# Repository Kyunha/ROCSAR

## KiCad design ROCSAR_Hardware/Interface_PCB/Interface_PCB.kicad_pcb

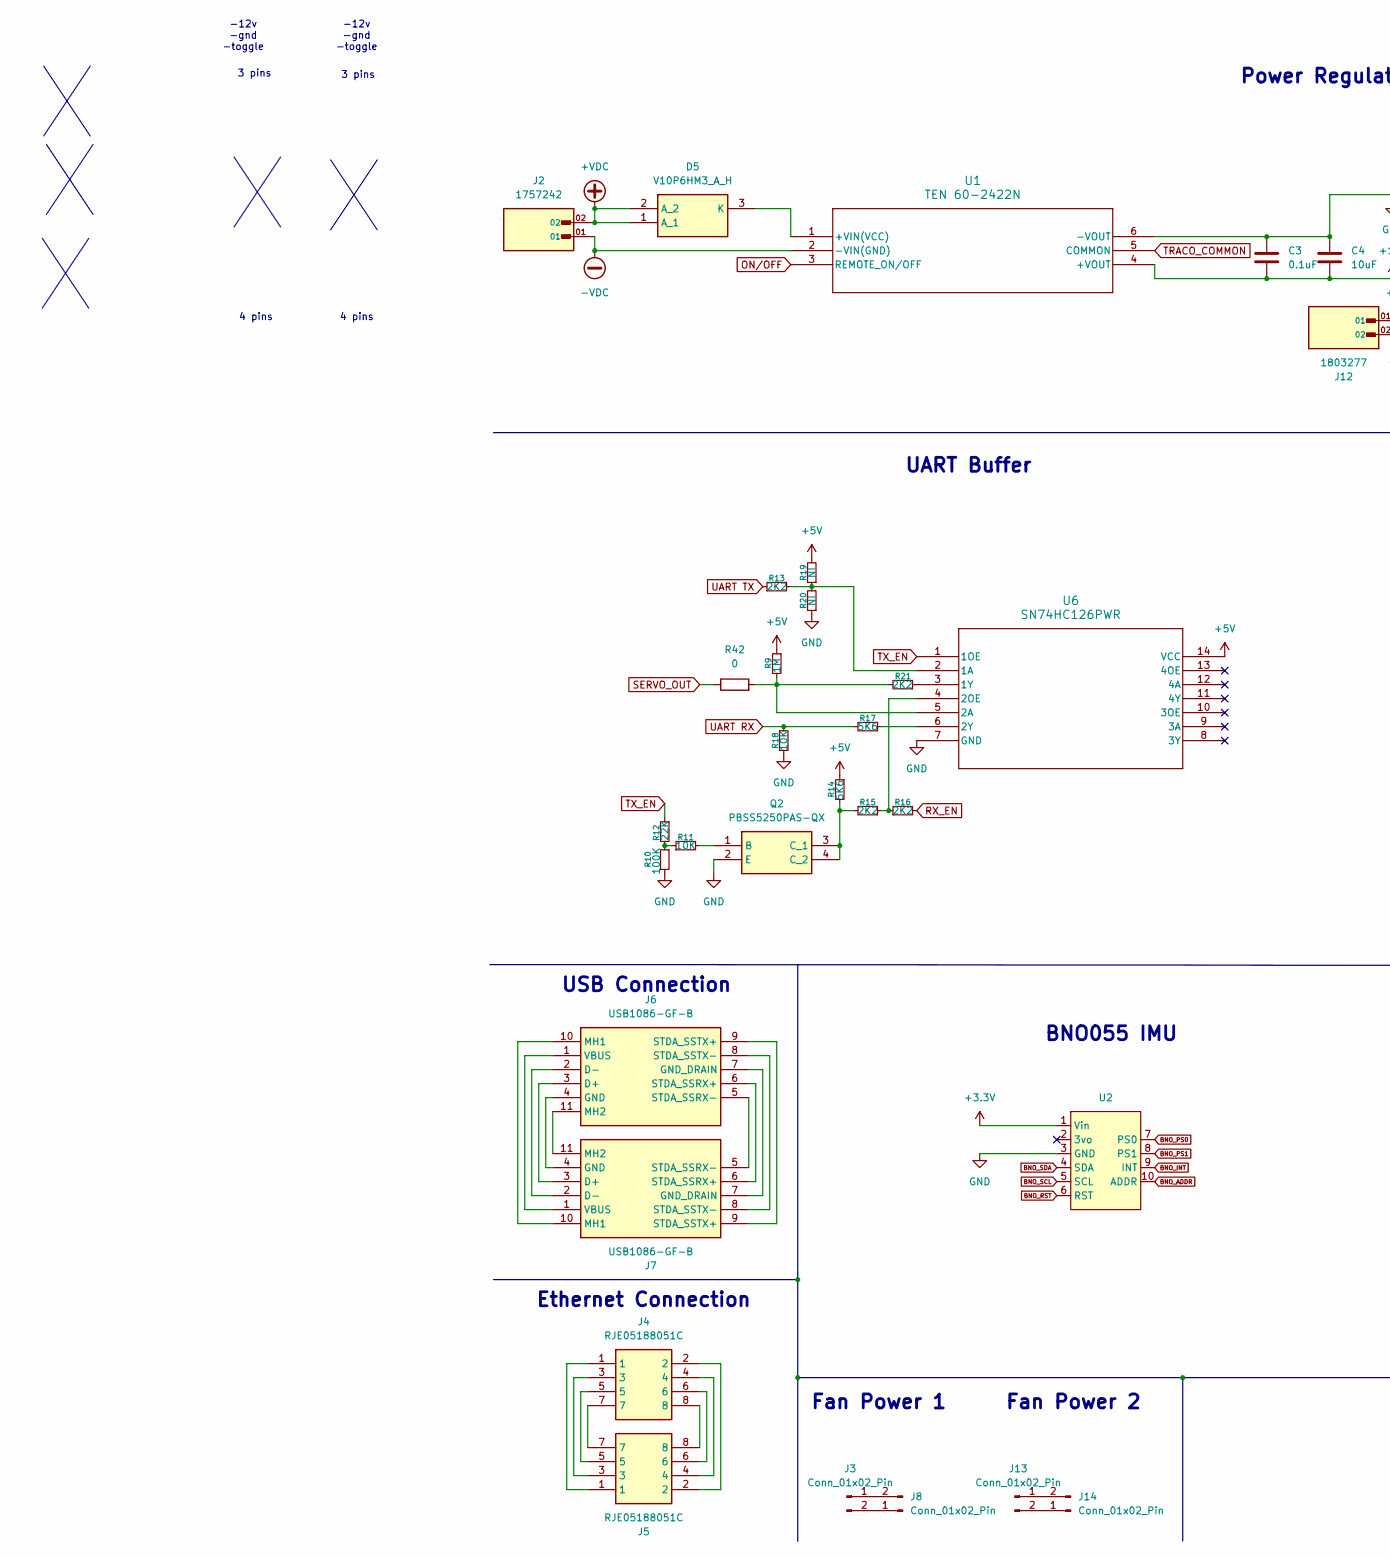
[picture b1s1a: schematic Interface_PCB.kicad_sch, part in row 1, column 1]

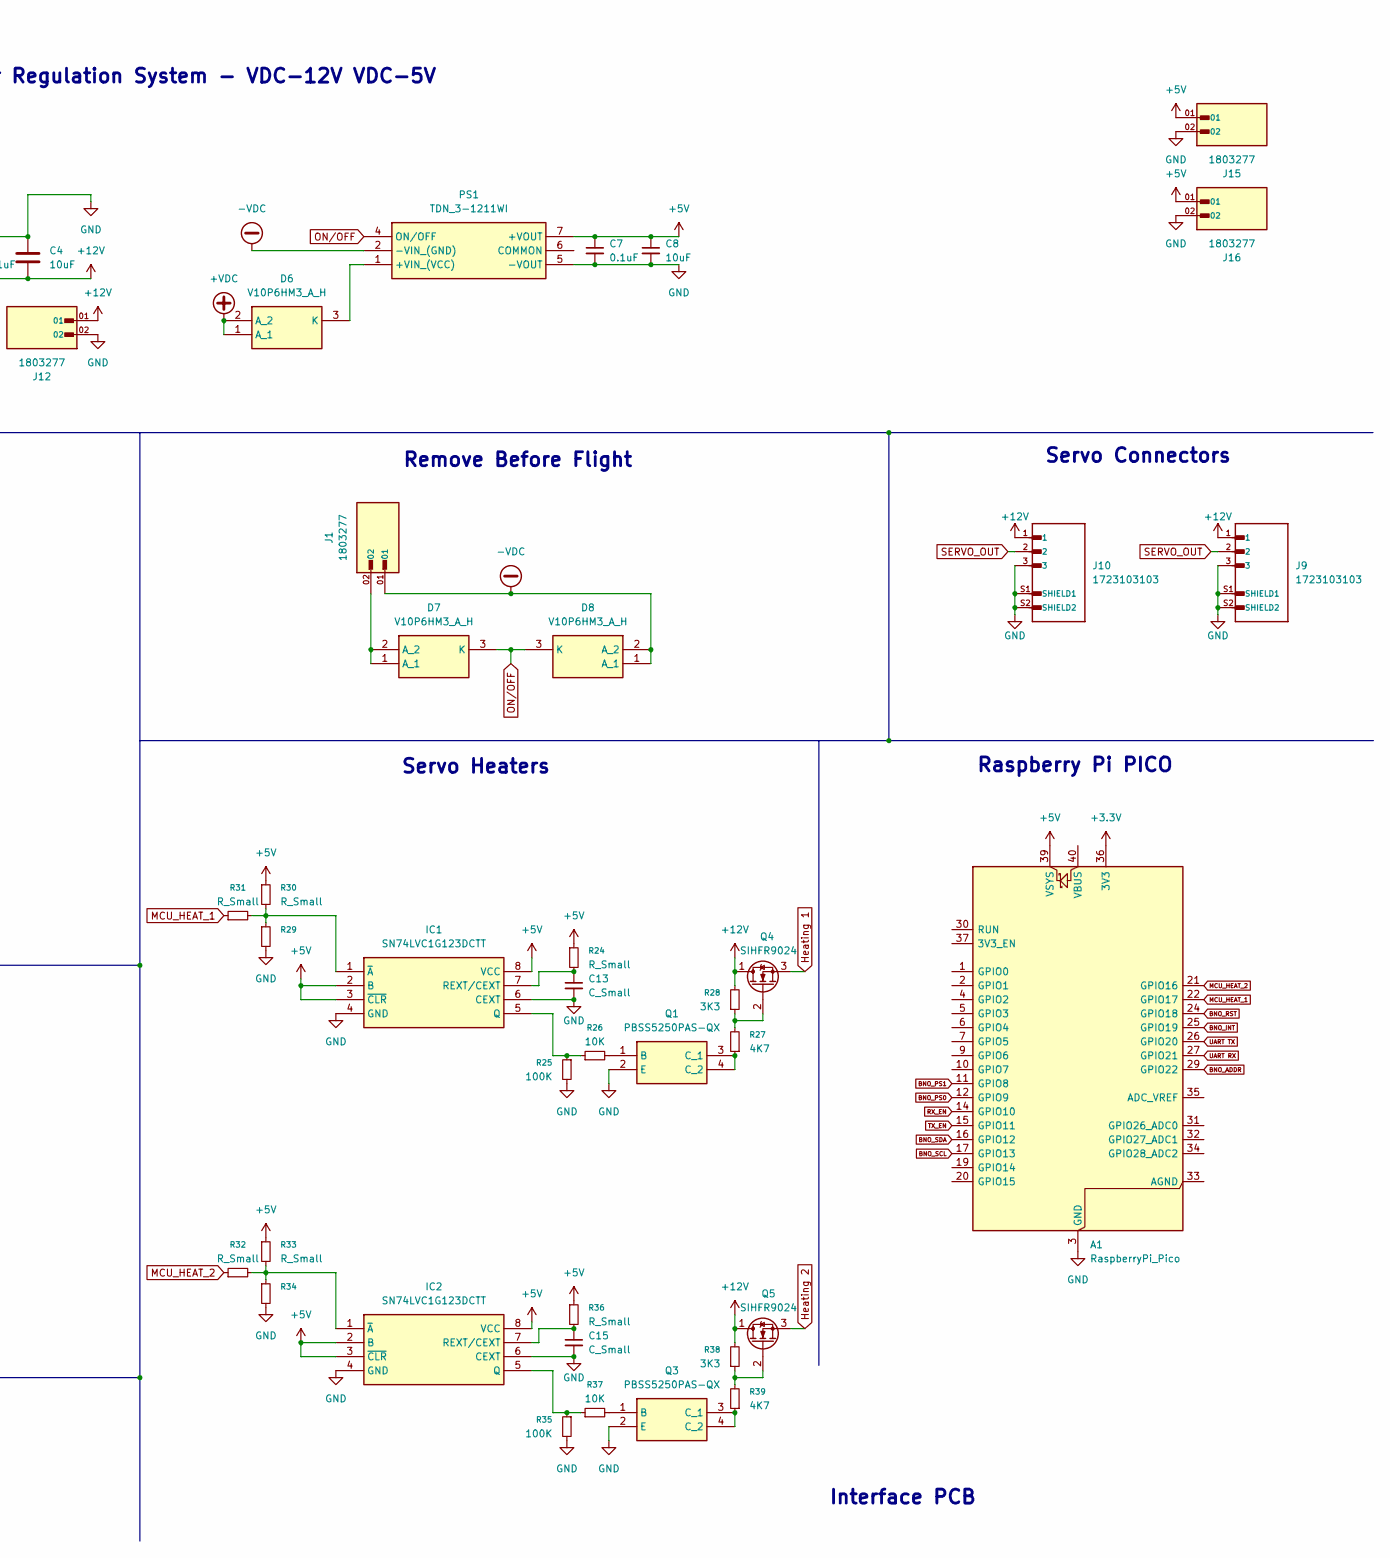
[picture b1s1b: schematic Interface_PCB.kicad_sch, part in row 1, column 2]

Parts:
A1: RaspberryPi_Pico; RaspberryPi_Pico_Common_Unspecified
C3, C7: 0.1uF; C_1206_3216Metric_Pad1.33x1.80mm_HandSolder
C4, C8: 10uF; C_1206_3216Metric_Pad1.33x1.80mm_HandSolder
C13, C15: C_Small; C_Radial_D10.0mm_H16.0mm_P5.00mm
D5, D6, D7, D8: V10P6HM3_A_H; V10P6HM3_AH; Mouser Part Number 78-V10P6HM3_A/H
IC1, IC2: SN74LVC1G123DCTT; SOP65P400X130-8N; Mouser Part Number 595-SN74LVC1G123DCTT
J1, J12, J15, J16: 1803277; PHOENIX_1803277
J2: 1757242; PHOENIX_1757242; PARTREV 28.07.2023
J3, J8, J13, J14: Conn_01x02_Pin; PinHeader_1x02_P2.54mm_Vertical
J4, J5: RJE05188051C; Manufacturer_Part_Number RJE05188051C
J6, J7: USB1086-GF-B; USB1086GFB; Mouser Part Number 640-USB1086-GF-B
J9, J10: 1723103103; MOLEX_1723103103; PARTREV B1; DigiKey_Part_Number 900-1723103103-ND
PS1: TDN_3-1211WI; TDN52412WI; Manufacturer_Part_Number TDN 3-1211WI; Mouser Part Number 495-TDN3-1211WI
Q1, Q2, Q3: PBSS5250PAS-QX; PMEG2020EPASX; Mouser Part Number 771-PBSS5250PAS-QX
Q4, Q5: SIHFR9024
R9: 1M; R_0603_1608Metric_Pad0.98x0.95mm_HandSolder
R10, R25, R35: 100K; R_0603_1608Metric_Pad0.98x0.95mm_HandSolder
R11, R18, R26, R37: 10K; R_0603_1608Metric_Pad0.98x0.95mm_HandSolder
R12: 22K; R_0603_1608Metric_Pad0.98x0.95mm_HandSolder
R13, R15, R16, R21: 2K2; R_0603_1608Metric_Pad0.98x0.95mm_HandSolder
R14, R17: 5K6; R_0603_1608Metric_Pad0.98x0.95mm_HandSolder
R19, R20: NI; R_0603_1608Metric_Pad0.98x0.95mm_HandSolder
R24, R30, R31, R32, R33, R36: R_Small; R_0603_1608Metric_Pad0.98x0.95mm_HandSolder
R27, R39: 4K7; R_0603_1608Metric_Pad0.98x0.95mm_HandSolder
R28, R38: 3K3; R_0603_1608Metric_Pad0.98x0.95mm_HandSolder
R29, R34: R_0603_1608Metric_Pad0.98x0.95mm_HandSolder
R42: 0; R_0603_1608Metric_Pad0.98x0.95mm_HandSolder
U1: TEN 60-2422N; TEN60N_TRP
U2: Adafruit BNO055
U6: SN74HC126PWR; PW14

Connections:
+3.3V: A1.36 (3V3), U2.1 (Vin)
+5V: A1.39 (VSYS), C7.1, C8.1, IC1.2 (B), IC1.3 (~CLR), IC1.8 (VCC), IC2.2 (B), IC2.3 (~CLR), IC2.8 (VCC), J15.01, J16.01, PS1.7 (+VOUT), R9.1, R14.1, R19.2, R24.1, R30.1, R33.1, R36.1, U6.14 (VCC)
+12V: C3.2, C4.2, J9.1, J10.1, J12.01, Q4.1 (D), Q5.1 (D), R28.2, R38.2, U1.4 (+VOUT)
+VDC: D5.1 (A_1), D5.2 (A_2), D6.1 (A_1), D6.2 (A_2), J2.02
-VDC: D8.1 (A_1), D8.2 (A_2), J1.01, J2.01, PS1.2 (-VIN_(GND)), U1.2 (-VIN(GND))
BNO_ADDR: A1.29 (GPIO22), U2.10 (ADDR)
BNO_INT: A1.25 (GPIO19), U2.9 (INT)
BNO_PS0: A1.12 (GPIO9), U2.7 (PS0)
BNO_PS1: A1.11 (GPIO8), U2.8 (PS1)
BNO_RST: A1.24 (GPIO18), U2.6 (RST)
BNO_SCL: A1.17 (GPIO13), U2.5 (SCL)
BNO_SDA: A1.16 (GPIO12), U2.4 (SDA)
GND: A1.3 (GND), A1.8 (GND), A1.13 (GND), A1.18 (GND), A1.23 (GND), A1.28 (GND), A1.38 (GND), C3.1, C4.1, C7.2, C8.2, C13.2, C15.2, IC1.4 (GND), IC1.6 (CEXT), IC2.4 (GND), IC2.6 (CEXT), J9.3, J9.S1 (SHIELD1), J9.S2 (SHIELD2), J10.3, J10.S1 (SHIELD1), J10.S2 (SHIELD2), J12.02, J15.02, J16.02, PS1.5 (-VOUT), Q1.2 (E), Q2.2 (E), Q3.2 (E), R10.2, R18.2, R20.1, R25.2, R29.2, R34.2, R35.2, U1.6 (-VOUT), U2.3 (GND), U6.7 (GND)
Heating 1: Q4.3 (S)
Heating 2: Q5.3 (S)
MCU_HEAT_1: A1.22 (GPIO17), R31.1
MCU_HEAT_2: A1.21 (GPIO16), R32.1
unnamed: D5.3 (K), U1.1 (+VIN(VCC))
unnamed: D6.3 (K), PS1.1 (+VIN_(VCC))
unnamed: D7.1 (A_1), D7.2 (A_2), J1.02
unnamed: IC1.5 (Q), R25.1, R26.1
unnamed: C13.1, IC1.7 (REXT/CEXT), R24.2
unnamed: IC1.1 (~A), R29.1, R30.2, R31.2
unnamed: IC2.5 (Q), R35.1, R37.1
unnamed: C15.1, IC2.7 (REXT/CEXT), R36.2
unnamed: IC2.1 (~A), R32.2, R33.2, R34.1
unnamed: J3.1, J8.2
unnamed: J3.2, J8.1
unnamed: J4.1, J5.1
unnamed: J4.2, J5.2
unnamed: J4.3, J5.3
unnamed: J4.4, J5.4
unnamed: J4.5, J5.5
unnamed: J4.6, J5.6
unnamed: J4.7, J5.7
unnamed: J4.8, J5.8
unnamed: J6.3 (D+), J7.3 (D+)
unnamed: J6.2 (D-), J7.2 (D-)
unnamed: J6.4 (GND), J7.4 (GND)
unnamed: J6.7 (GND_DRAIN), J7.7 (GND_DRAIN)
unnamed: J6.10 (MH1), J7.10 (MH1)
unnamed: J6.11 (MH2), J7.11 (MH2)
unnamed: J6.6 (STDA_SSRX+), J7.6 (STDA_SSRX+)
unnamed: J6.5 (STDA_SSRX-), J7.5 (STDA_SSRX-)
unnamed: J6.9 (STDA_SSTX+), J7.9 (STDA_SSTX+)
unnamed: J6.8 (STDA_SSTX-), J7.8 (STDA_SSTX-)
unnamed: J6.1 (VBUS), J7.1 (VBUS)
unnamed: J13.1, J14.2
unnamed: J13.2, J14.1
unnamed: Q1.1 (B), R26.2
unnamed: Q1.3 (C_1), Q1.4 (C_2), R27.1
unnamed: Q2.1 (B), R11.2
unnamed: Q2.3 (C_1), Q2.4 (C_2), R14.2, R15.2
unnamed: Q3.1 (B), R37.2
unnamed: Q3.3 (C_1), Q3.4 (C_2), R39.1
unnamed: Q4.2 (G), R27.2, R28.1
unnamed: Q5.2 (G), R38.1, R39.2
unnamed: R10.1, R11.1, R12.2
unnamed: R13.2, R19.1, R20.2, U6.2 (1A)
unnamed: R21.1, U6.3 (1Y)
unnamed: R9.2, R21.2, R42.2, U6.5 (2A)
unnamed: R15.1, R16.1, U6.4 (2OE)
unnamed: R17.1, U6.6 (2Y)
ON/OFF: D7.3 (K), D8.3 (K), PS1.4 (ON/OFF), U1.3 (REMOTE_ON/OFF)
RX_EN: A1.14 (GPIO10), R16.2
SERVO_OUT: J9.2, J10.2, R42.1
TRACO_COMMON: U1.5 (COMMON)
TX_EN: A1.15 (GPIO11), R12.1, U6.1 (1OE)
UART RX: A1.27 (GPIO21), R17.2, R18.1
UART TX: A1.26 (GPIO20), R13.1

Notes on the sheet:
4 pins
BNO055 IMU
-12v -gnd -toggle
Fan Power 1
USB Connection
3 pins
Servo Heaters
Interface PCB
UART Buffer
Servo Connectors
Power Regulation System - VDC-12V VDC-5V
Fan Power 2
Ethernet Connection
Raspberry Pi PICO
Remove Before Flight

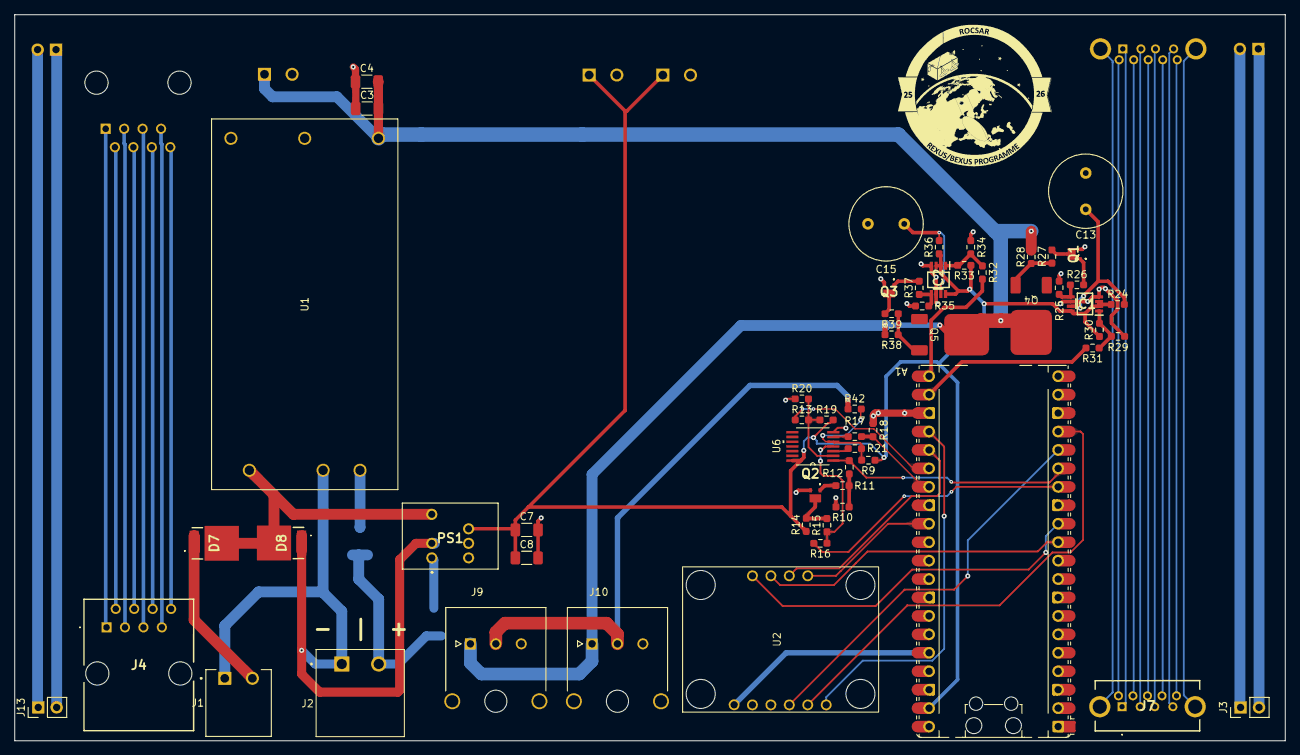
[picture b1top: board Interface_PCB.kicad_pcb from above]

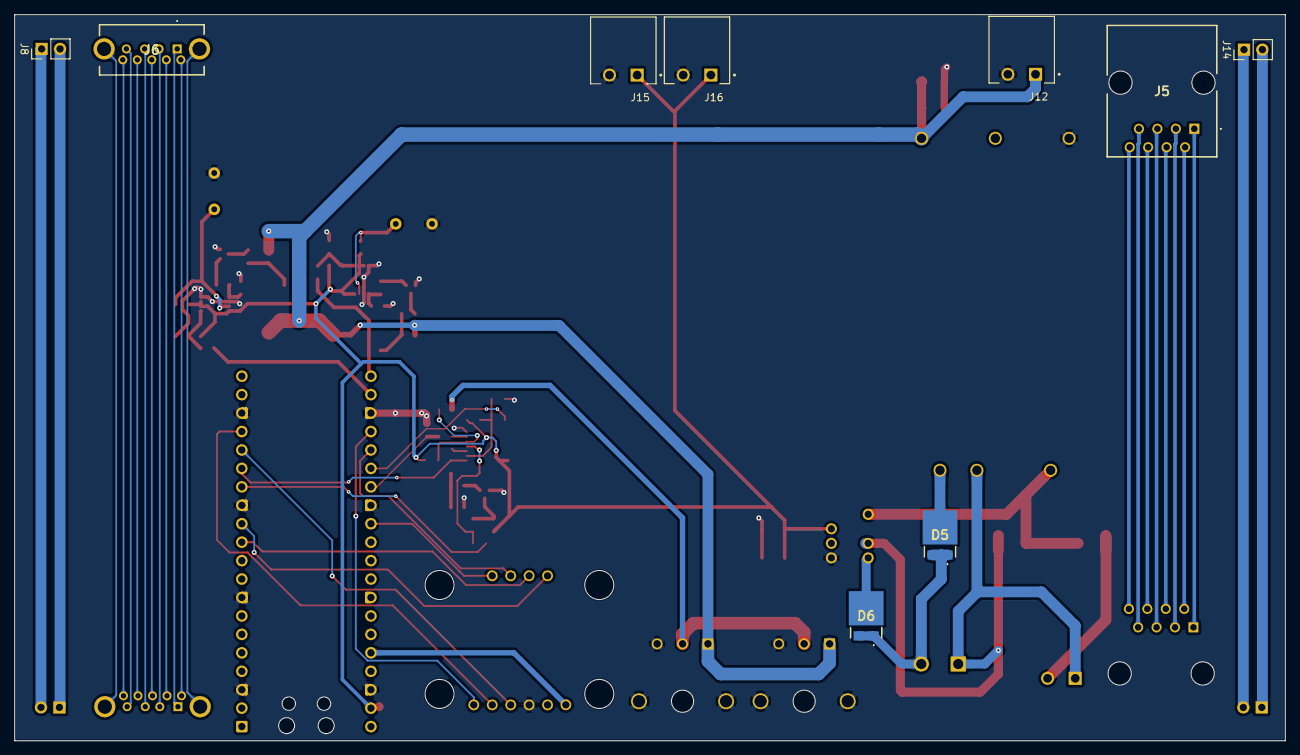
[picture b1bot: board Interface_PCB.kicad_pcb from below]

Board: 2 copper layers, 175.0 x 100.0 mm, 67 parts (9 on the bottom side), 67 nets.

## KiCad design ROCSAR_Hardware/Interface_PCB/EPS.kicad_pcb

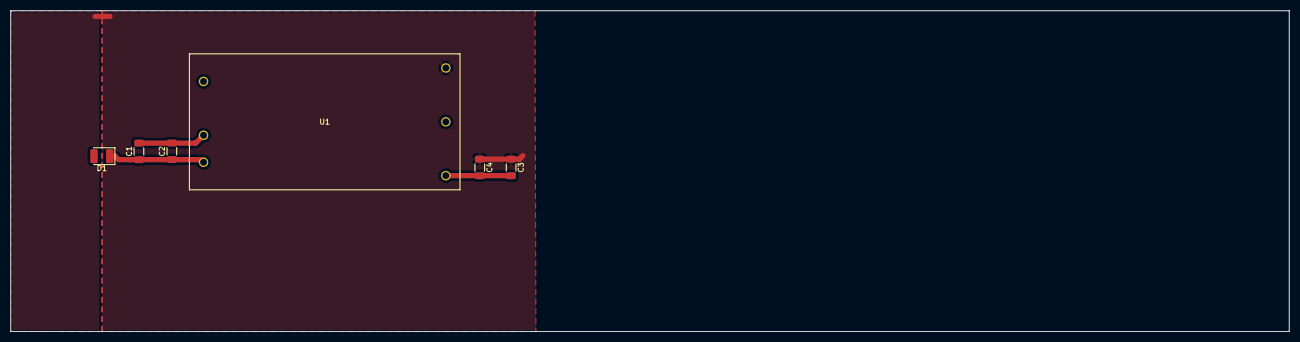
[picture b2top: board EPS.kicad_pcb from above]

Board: 2 copper layers, 241.2 x 60.5 mm, 6 parts (0 on the bottom side), 4 nets.

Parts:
C1, C3: 0.1uF; C_1206_3216Metric_Pad1.33x1.80mm_HandSolder
C2, C4: 10uF; C_1206_3216Metric_Pad1.33x1.80mm_HandSolder
D1: D; D_1210_3225Metric_Pad1.42x2.65mm_HandSolder
U1: TEN 60-2422N; TEN60N_TRP

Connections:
+12V: C3.2, C4.2, U1.4 (+VOUT)
GND: C3.1, C4.1, U1.6 (-VOUT)
GND1: C1.2, C2.2, U1.2 (-VIN(GND))
unnamed: C1.1, C2.1, D1.1 (K), U1.1 (+VIN(VCC))

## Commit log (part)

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2026-03-22 PCB Interface
2026-03-22 interface
2026-03-28 PCB Update
2026-04-16 Continuation of the development of the interface pcb
2026-04-18 Interface PCB mostly done
2026-05-03 atualizacoes interface
2026-05-15 Interface Updates
